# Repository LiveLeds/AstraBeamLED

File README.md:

# AstraBeamLED

[GitHub IO Page](https://liveleds.github.io/AstraBeamLED)

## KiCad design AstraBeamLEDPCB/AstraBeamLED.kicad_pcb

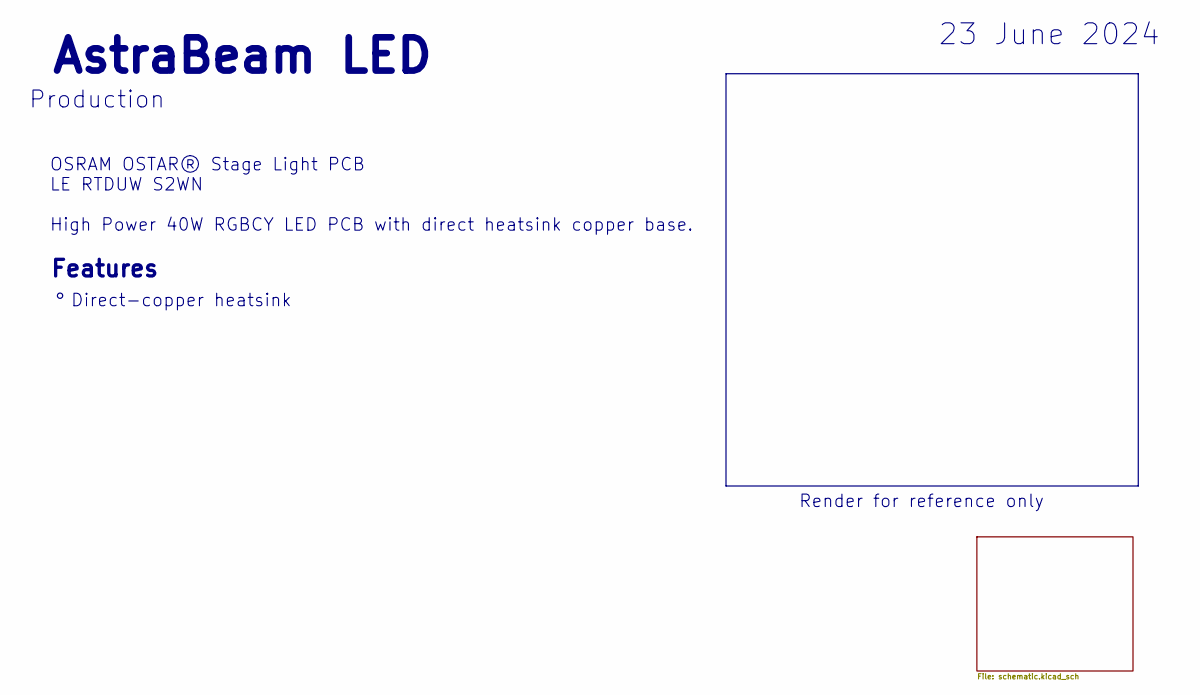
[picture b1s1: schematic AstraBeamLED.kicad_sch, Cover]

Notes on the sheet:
Features
OSRAM OSTAR® Stage Light PCB LE RTDUW S2WN High Power 40W RGBCY LED PCB with direct heatsink copper base.
AstraBeam LED
Direct-copper heatsink
Render for reference only
Production
23 June 2024

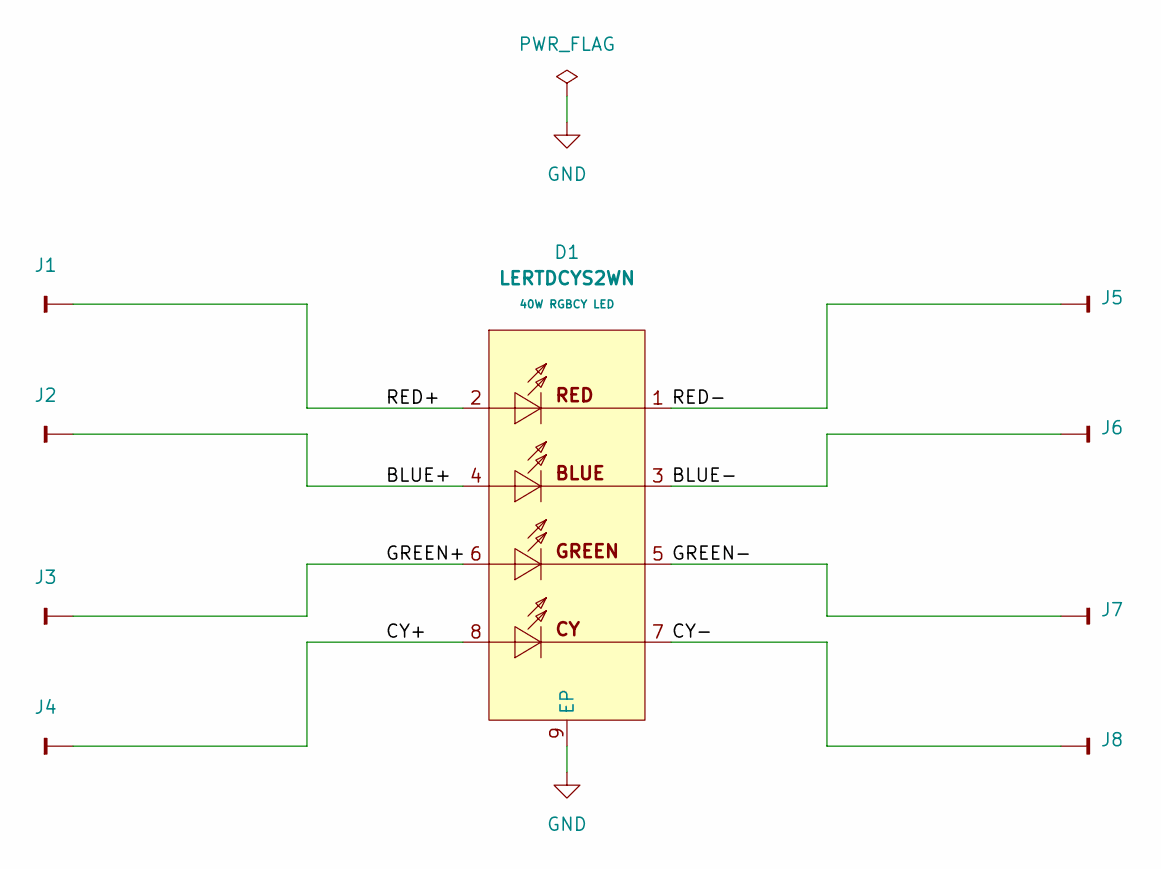
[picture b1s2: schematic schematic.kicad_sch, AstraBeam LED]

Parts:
D1: LERTDCYS2WN; LED_LERTDCYS2WN; MPN LERTDCYS2WN-KBLA-1+MANA-P+AXAZ-3+LBMB-YS; LCSC Part C2899869
J1, J2, J3, J4, J5, J6, J7, J8: SolderWirePad_1x01_SMD_5x10mm

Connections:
/Schematic/BLUE+: D1.4, J2.1
/Schematic/BLUE-: D1.3, J6.1
/Schematic/CY+: D1.8, J4.1
/Schematic/CY-: D1.7, J8.1
/Schematic/GREEN+: D1.6, J3.1
/Schematic/GREEN-: D1.5, J7.1
/Schematic/RED+: D1.2, J1.1
/Schematic/RED-: D1.1, J5.1
GND: D1.9 (EP)

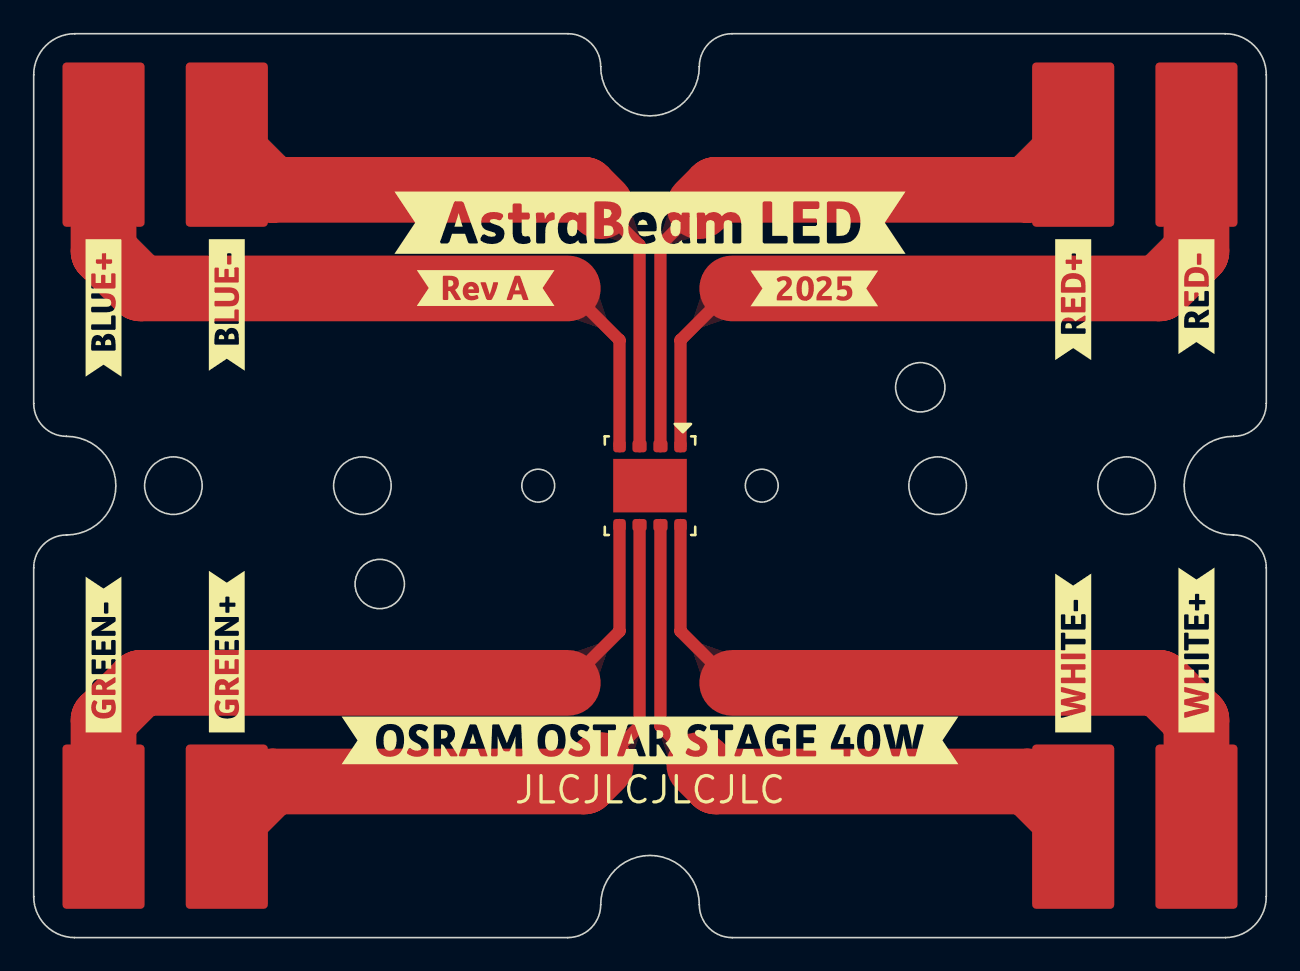
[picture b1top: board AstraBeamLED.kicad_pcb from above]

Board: 2 copper layers, 75.0 x 55.0 mm, 21 parts (0 on the bottom side), 8 nets.

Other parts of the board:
kibuzzard-678EC3F2: G***; kibuzzard-678EC3F2
kibuzzard-678EC518: G***; kibuzzard-678EC518
kibuzzard-67294BDE: G***; kibuzzard-67294BDE
kibuzzard-67294BF2: G***; kibuzzard-67294BF2
kibuzzard-68162CBA: G***; kibuzzard-68162CBA
kibuzzard-68162CC4: G***; kibuzzard-68162CC4
kibuzzard-68162CCF: G***; kibuzzard-68162CCF
kibuzzard-68162CD6: G***; kibuzzard-68162CD6
kibuzzard-68162D5D: G***; kibuzzard-68162D5D
kibuzzard-68162D21: G***; kibuzzard-68162D21
kibuzzard-68162D41: G***; kibuzzard-68162D41
kibuzzard-68162D54: G***; kibuzzard-68162D54

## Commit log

2024-11-03 Fix pcb print
2024-11-03 Rename layer to heat-sink
2024-11-03 Added ti connectors
2024-11-04 Redesigned pcb for smaller size
2024-11-04 Updated step path
2024-11-04 Improve render
2024-11-05 Update for render
2024-11-05 holes 29mm instead of 30mm
2024-11-05 Tweaks
2024-11-05 tweak heatsink
2024-11-05 Save updates
2024-11-08 Updated to invisible wrl
2024-11-08 LED step is messed up
2025-01-20 Cleanup
2025-01-20 fix font
2025-01-20 Add 40W
2025-01-23 Tweak mounting holes
2025-02-07 Updated layout
2025-02-08 Extra tweaks to copper
2025-02-08 Bring back tear drops
2025-04-01 Updated fcu copper heat sink
2025-04-04 removed mark from direct heatsink layer
2025-04-07 Cleanup copper for production
2025-05-02 Fix reversed pins
2025-05-02 Update with post production report
2025-05-03 Updated labels, description
2025-05-03 Update render
2025-05-03 update renders
2025-05-03 Update finish
2025-05-03 Updated datasheet render
